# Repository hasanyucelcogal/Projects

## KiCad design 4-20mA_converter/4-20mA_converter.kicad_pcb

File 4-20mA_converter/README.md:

~~SPECS~~
* Configurable Output Current Limitting
* Industrial Components
* 0-10V or 4-20 mA mode Selecting

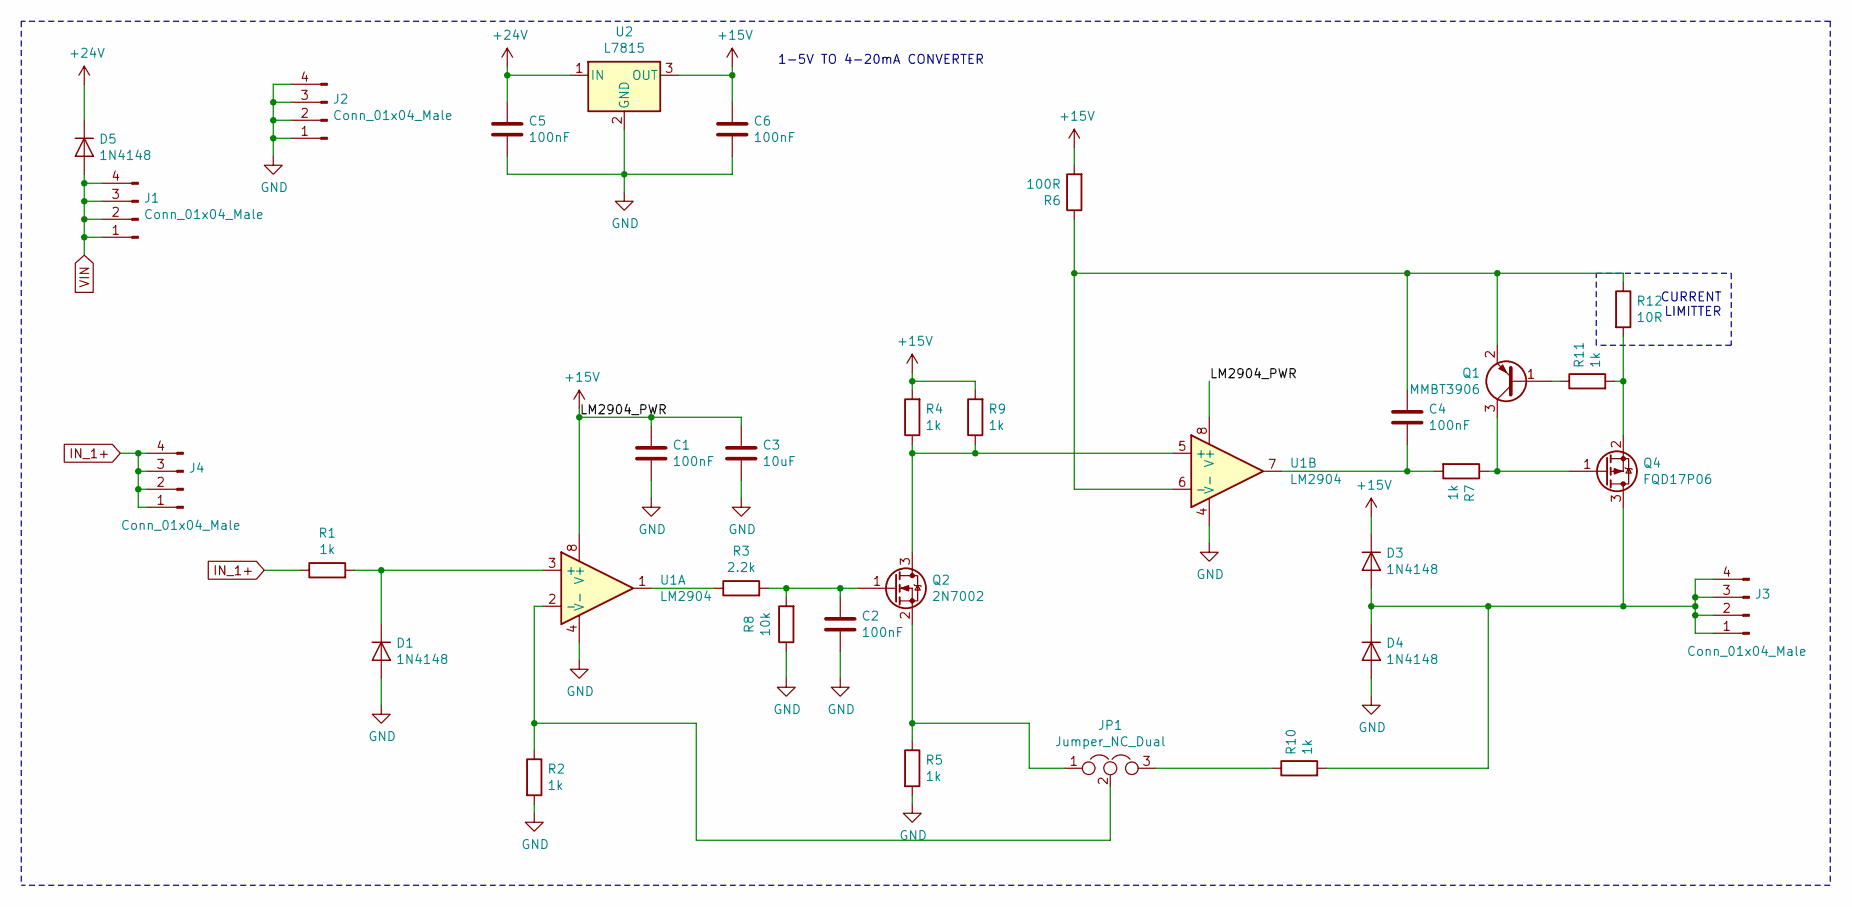
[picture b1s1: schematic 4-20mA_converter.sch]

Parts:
C1, C2, C4, C5, C6: 100nF; C_0603_1608Metric
C3: 10uF; C_0603_1608Metric
D1, D3, D4, D5: 1N4148; R_1206_3216Metric
J1, J2, J4: Conn_01x04_Male; PinHeader_1x04_P2.54mm_Vertical_SMD_Pin1Right
J3: Conn_01x04_Male; PinHeader_1x04_P2.00mm_Vertical_SMD_Pin1Left
JP1: Jumper_NC_Dual; PinHeader_1x03_P2.54mm_Vertical
Q1: MMBT3906; SOT-23
Q2: 2N7002; SOT-23
Q4: FQD17P06; TO-252-2
R1, R2, R4, R5, R7, R9, R10, R11: 1k; R_0603_1608Metric
R3: 2.2k; R_0603_1608Metric
R6: 100R; R_0603_1608Metric
R8: 10k; R_0603_1608Metric
R12: 10R; R_0603_1608Metric
U1: LM2904; SOIC-8_3.9x4.9mm_P1.27mm
U2: L7815; TO-220-3_Vertical

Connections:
+15V: C1.1, C3.1, C6.1, D3.1 (K), R4.2, R6.2, R9.2, U1.8 (V+), U2.3 (OUT)
+24V: C5.1, D5.1 (K), U2.1 (IN)
GND: C1.2, C2.2, C3.2, C5.2, C6.2, D1.2 (A), D4.2 (A), J2.1, J2.2, J2.3, J2.4, R2.2, R5.2, R8.1, U1.4 (V-), U2.2 (GND)
IN_1+: J4.1, J4.2, J4.3, J4.4, R1.1
unnamed: C2.1, Q2.1 (G), R3.2, R8.2
unnamed: C4.1, Q1.2 (E), R6.1, R12.1, U1.6 (-)
unnamed: C4.2, R7.2, U1.7
unnamed: D1.1 (K), R1.2, U1.3 (+)
unnamed: D3.2 (A), D4.1 (K), J3.1, J3.2, J3.3, J3.4, Q4.3, R10.2
unnamed: JP1.1, Q2.2 (S), R5.1
unnamed: JP1.2, R2.1, U1.2 (-)
unnamed: JP1.3, R10.1
unnamed: Q1.1 (B), R11.1
unnamed: Q1.3 (C), Q4.1, R7.1
unnamed: Q2.3 (D), R4.1, R9.1, U1.5 (+)
unnamed: Q4.2, R11.2, R12.2
unnamed: R3.1, U1.1
VIN: D5.2 (A), J1.1, J1.2, J1.3, J1.4

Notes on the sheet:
1-5V TO 4-20mA CONVERTER
CURRENT LIMITTER

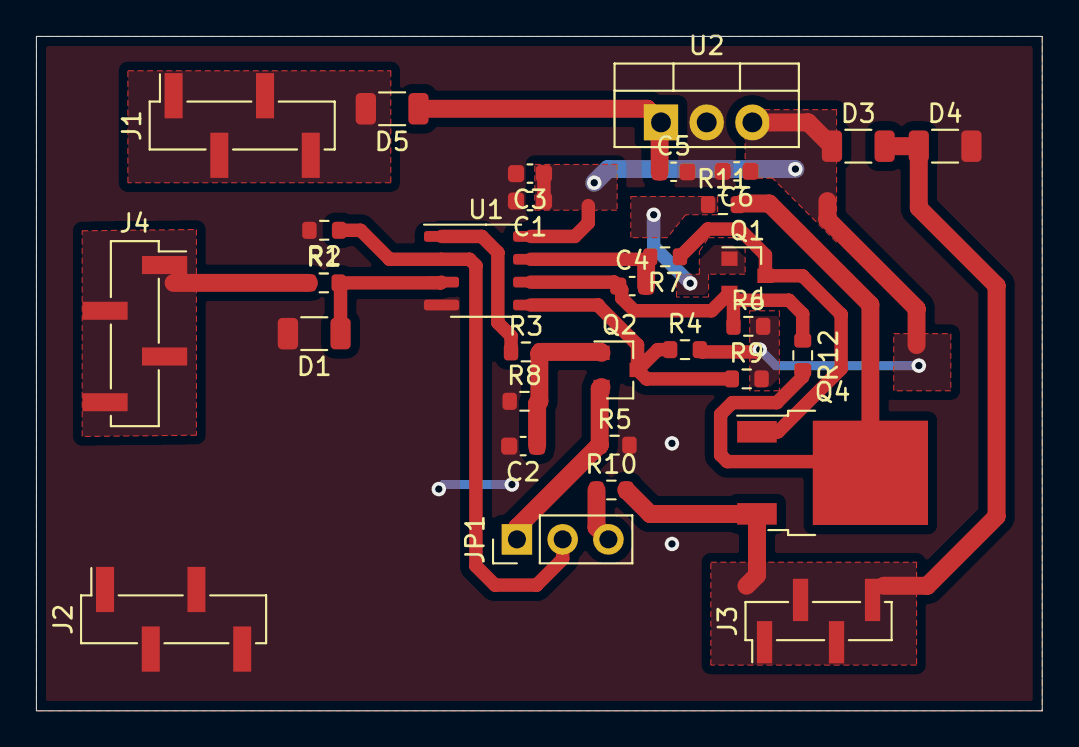
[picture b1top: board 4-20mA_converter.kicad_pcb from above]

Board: 2 copper layers, 55.9 x 37.5 mm, 32 parts (0 on the bottom side), 18 nets.

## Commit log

2021-11-17 projects
2021-12-07 Add files via upload
    4-20 mA converter
2022-03-14 Add files via upload
    ac peak to peak current monitor
2022-03-17 Create AC Current Monitor
2022-03-17 AC Current Monitor
2022-04-06 demo pcb
2022-05-08 Specs Added
2022-05-08 Readme Added
2022-05-08 GUI files added
2022-05-11 state comparator
